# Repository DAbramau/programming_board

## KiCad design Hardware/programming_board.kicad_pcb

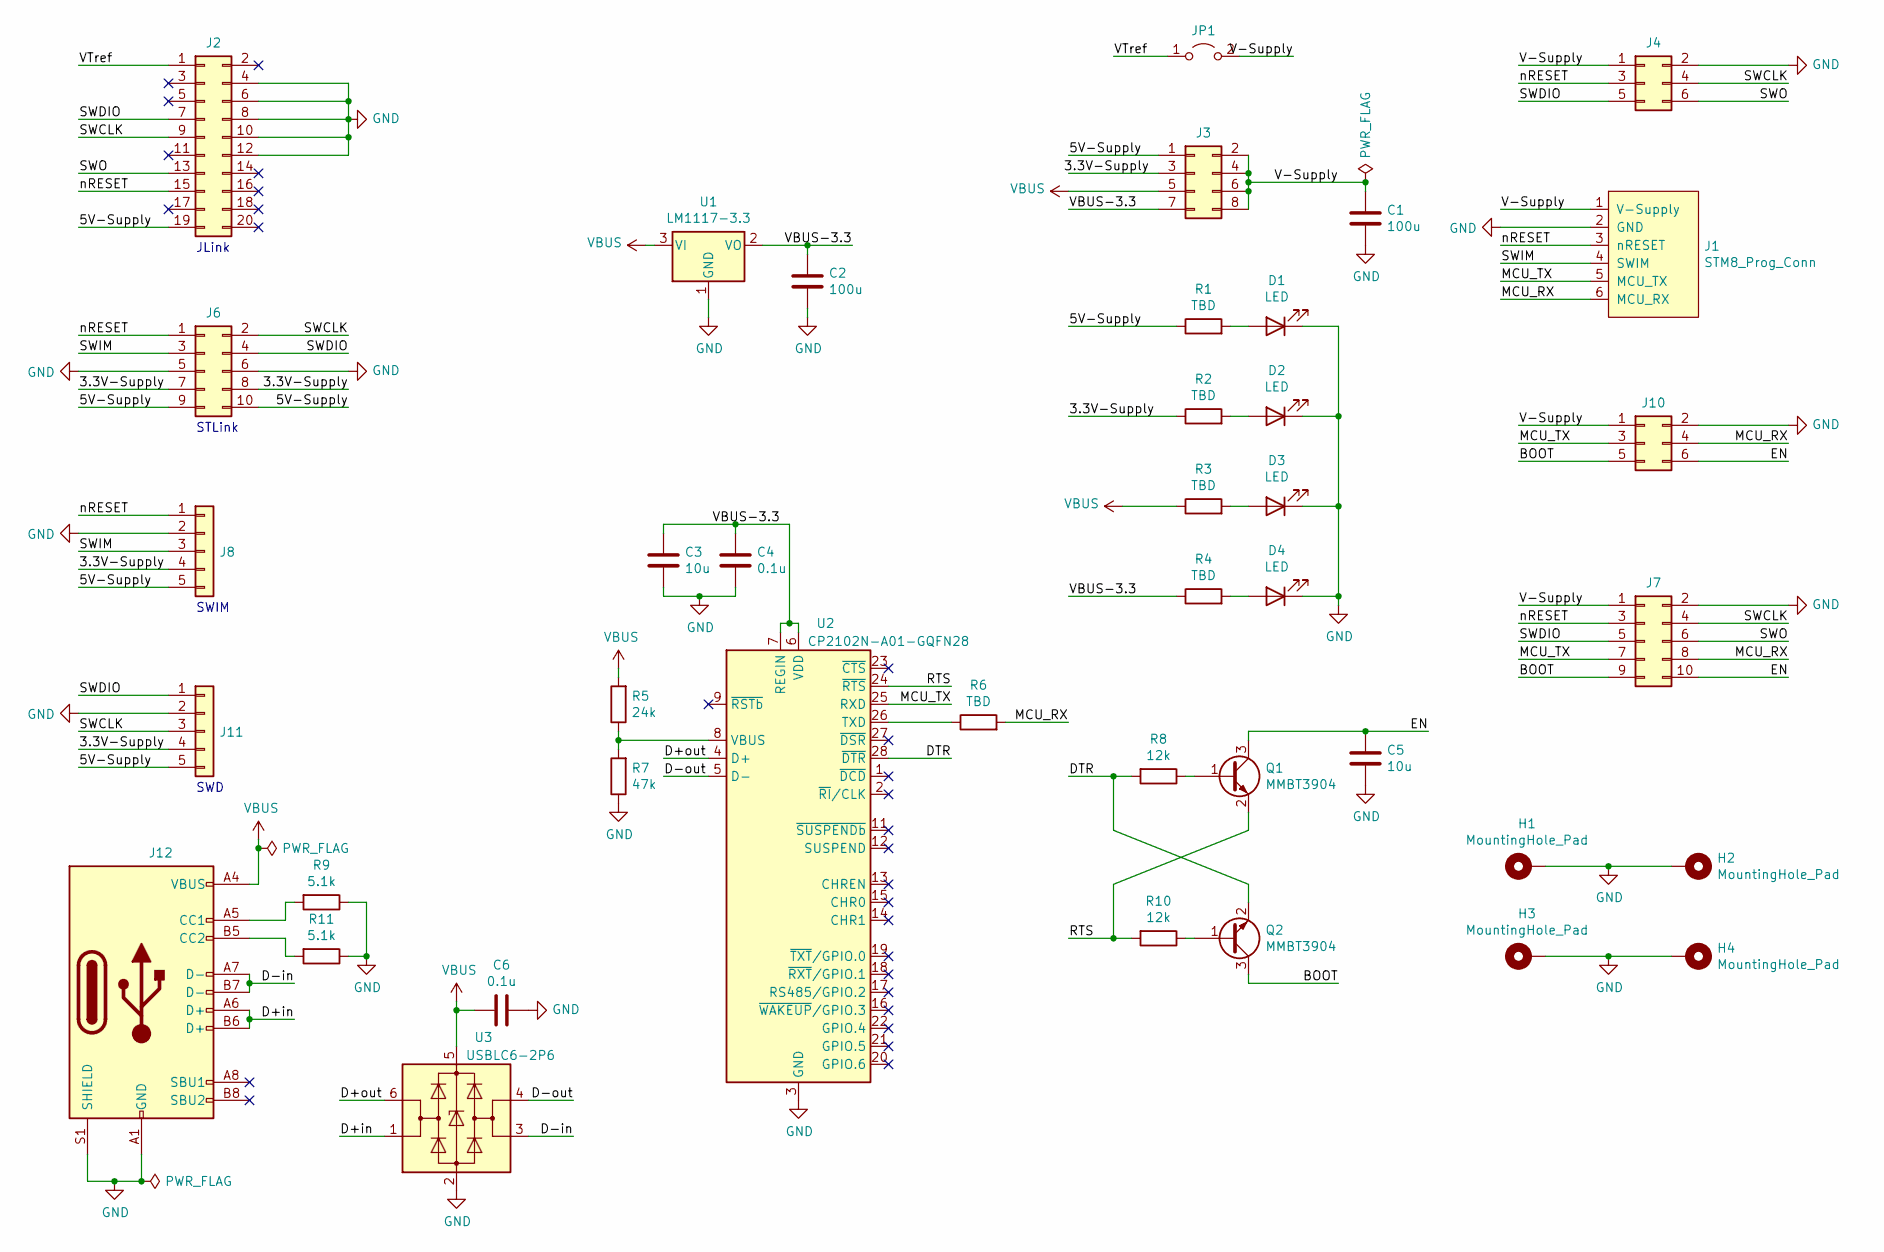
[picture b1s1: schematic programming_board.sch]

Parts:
C1, C2: 100u; C_1206_3216Metric_Pad1.33x1.80mm_HandSolder
C3, C5: 10u; C_0805_2012Metric_Pad1.15x1.40mm_HandSolder
C4, C6: 0.1u; C_0805_2012Metric_Pad1.15x1.40mm_HandSolder
D1, D2, D3, D4: LED; LED_0805_2012Metric
H1, H2, H3, H4: MountingHole_Pad; MountingHole_3.2mm_M3_Pad_Via
J1: STM8_Prog_Conn; IDC-1.27-6P
J2: Conn_02x10_Odd_Even; IDC-Header_2x10_P2.54mm_Vertical
J3: Conn_02x04_Odd_Even; PinHeader_2x04_P2.54mm_Vertical
J4, J10: Conn_02x03_Odd_Even; IDC-1.27-6P
J6: Conn_02x05_Odd_Even; IDC-Header_2x05_P2.54mm_Vertical
J7: Conn_02x05_Odd_Even; IDC-1.27-10P
J8, J11: Conn_01x05; PinHeader_1x05_P2.54mm_Vertical
J12: USB_C_Receptacle_USB2.0; USB_C_Receptacle_HRO_TYPE-C-31-M-12
JP1: Jumper_2_Open; PinHeader_1x02_P2.54mm_Vertical
Q1, Q2: MMBT3904; SOT-23
R1, R2, R3, R4, R6: TBD; R_0805_2012Metric_Pad1.15x1.40mm_HandSolder
R5: 24k; R_0805_2012Metric_Pad1.15x1.40mm_HandSolder
R7: 47k; R_0805_2012Metric_Pad1.15x1.40mm_HandSolder
R8, R10: 12k; R_0805_2012Metric_Pad1.15x1.40mm_HandSolder
R9, R11: 5.1k; R_0805_2012Metric_Pad1.15x1.40mm_HandSolder
U1: LM1117-3.3; SOT-223-3_TabPin2
U2: CP2102N-A01-GQFN28; QFN-28-1EP_5x5mm_P0.5mm_EP3.35x3.35mm
U3: USBLC6-2P6; SOT-666

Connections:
/3.3V-Supply: J3.3, J6.7, J6.8, J8.4, J11.4, R2.1
/5V-Supply: J2.19, J3.1, J6.9, J6.10, J8.5, J11.5, R1.1
/BOOT: J7.9, J10.5, Q2.3 (C)
/D+in: J12.A6 (D+), J12.B6 (D+), U3.1 (I/O1)
/D+out: U2.4 (D+), U3.6 (I/O1)
/D-in: J12.A7 (D-), J12.B7 (D-), U3.3 (I/O2)
/D-out: U2.5 (D-), U3.4 (I/O2)
/DTR: Q2.2 (E), R8.2, U2.28 (~DTR)
/EN: C5.1, J7.10, J10.6, Q1.3 (C)
/MCU_RX: J1.6 (MCU_RX), J7.8, J10.4, R6.2
/MCU_TX: J1.5 (MCU_TX), J7.7, J10.3, U2.25 (RXD)
/RTS: Q1.2 (E), R10.2, U2.24 (~RTS)
/SWCLK: J2.9, J4.4, J6.2, J7.4, J11.3
/SWDIO: J2.7, J4.5, J6.4, J7.5, J11.1
/SWIM: J1.4 (SWIM), J6.3, J8.3
/SWO: J2.13, J4.6, J7.6
/V-Supply: C1.1, J1.1 (V-Supply), J3.2, J3.4, J3.6, J3.8, J4.1, J7.1, J10.1, JP1.2 (B)
/VBUS-3.3: C2.1, C3.1, C4.1, J3.7, R4.1, U1.2 (VO), U2.6 (VDD), U2.7 (REGIN)
/VTref: J2.1, JP1.1 (A)
/nRESET: J1.3 (nRESET), J2.15, J4.3, J6.1, J7.3, J8.1
GND: C1.2, C2.2, C3.2, C4.2, C5.2, C6.2, D1.1 (K), D2.1 (K), D3.1 (K), D4.1 (K), H1.1, H2.1, H3.1, H4.1, J1.2 (GND), J2.4, J2.6, J2.8, J2.10, J2.12, J4.2, J6.5, J6.6, J7.2, J8.2, J10.2, J11.2, J12.A1 (GND), J12.A12 (GND), J12.B1 (GND), J12.B12 (GND), J12.S1 (SHIELD), R7.1, R9.1, R11.1, U1.1 (GND), U2.3 (GND), U2.29 (GND), U3.2 (GND)
unnamed: D1.2 (A), R1.2
unnamed: D2.2 (A), R2.2
unnamed: D3.2 (A), R3.2
unnamed: D4.2 (A), R4.2
unnamed: J12.A5 (CC1), R9.2
unnamed: J12.B5 (CC2), R11.2
unnamed: Q1.1 (B), R8.1
unnamed: Q2.1 (B), R10.1
unnamed: R5.1, R7.2, U2.8 (VBUS)
unnamed: R6.1, U2.26 (TXD)
VBUS: C6.1, J3.5, J12.A4 (VBUS), J12.A9 (VBUS), J12.B4 (VBUS), J12.B9 (VBUS), R3.1, R5.2, U1.3 (VI), U3.5 (VBUS)

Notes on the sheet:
SWIM
SWD
STLink
JLink

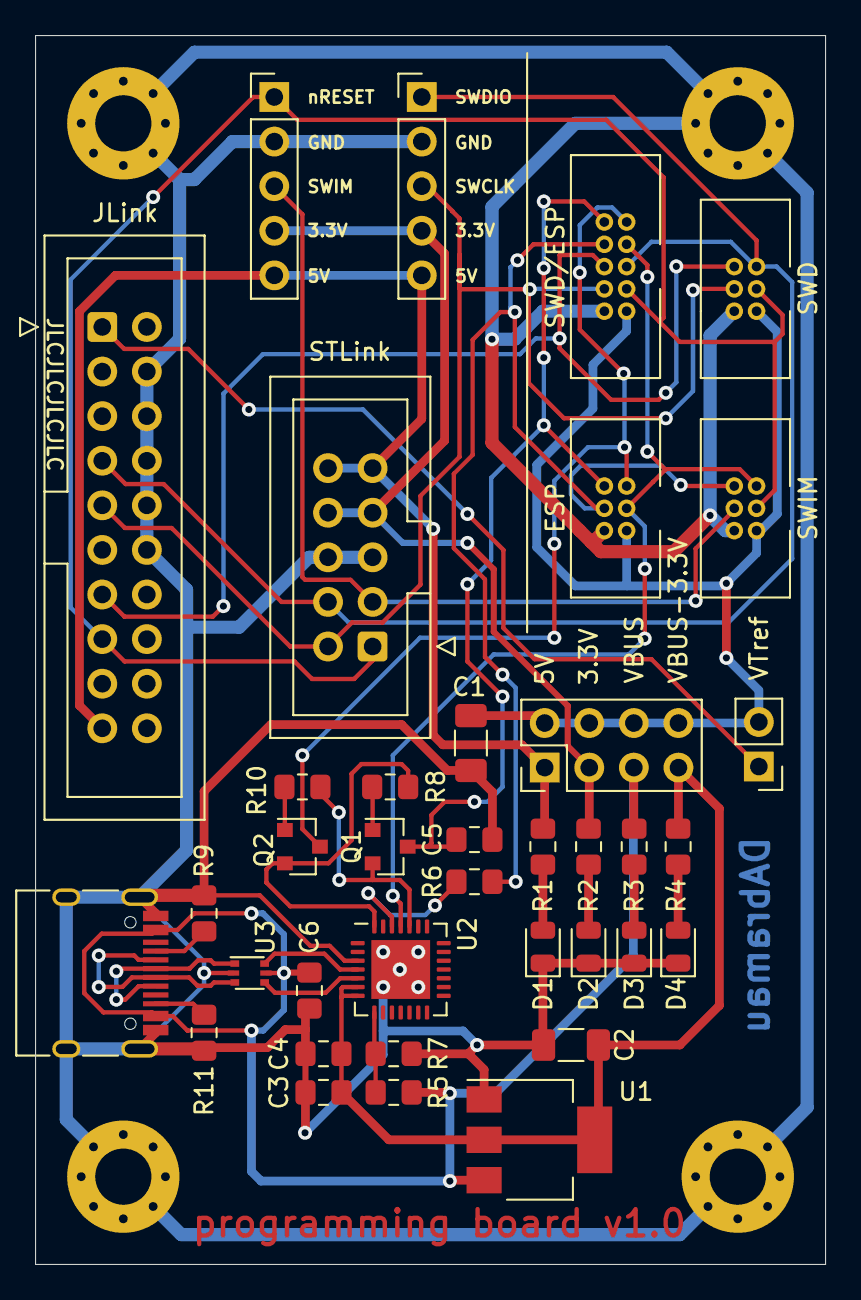
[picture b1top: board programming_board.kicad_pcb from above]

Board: 2 copper layers, 45.0 x 70.0 mm, 41 parts (0 on the bottom side), 32 nets.

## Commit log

2021-09-26 remove pcb backup
2021-09-26 remove fp-info-cache; add cache.lib
2021-09-26 rearrange files; add documents
2021-09-26 add stlink cone image
2021-09-26 add stm8 programming connector; add 3d models
2021-09-26 fix drc
2021-10-05 remove connector number from silkS
2021-10-05 add Production v1.0
